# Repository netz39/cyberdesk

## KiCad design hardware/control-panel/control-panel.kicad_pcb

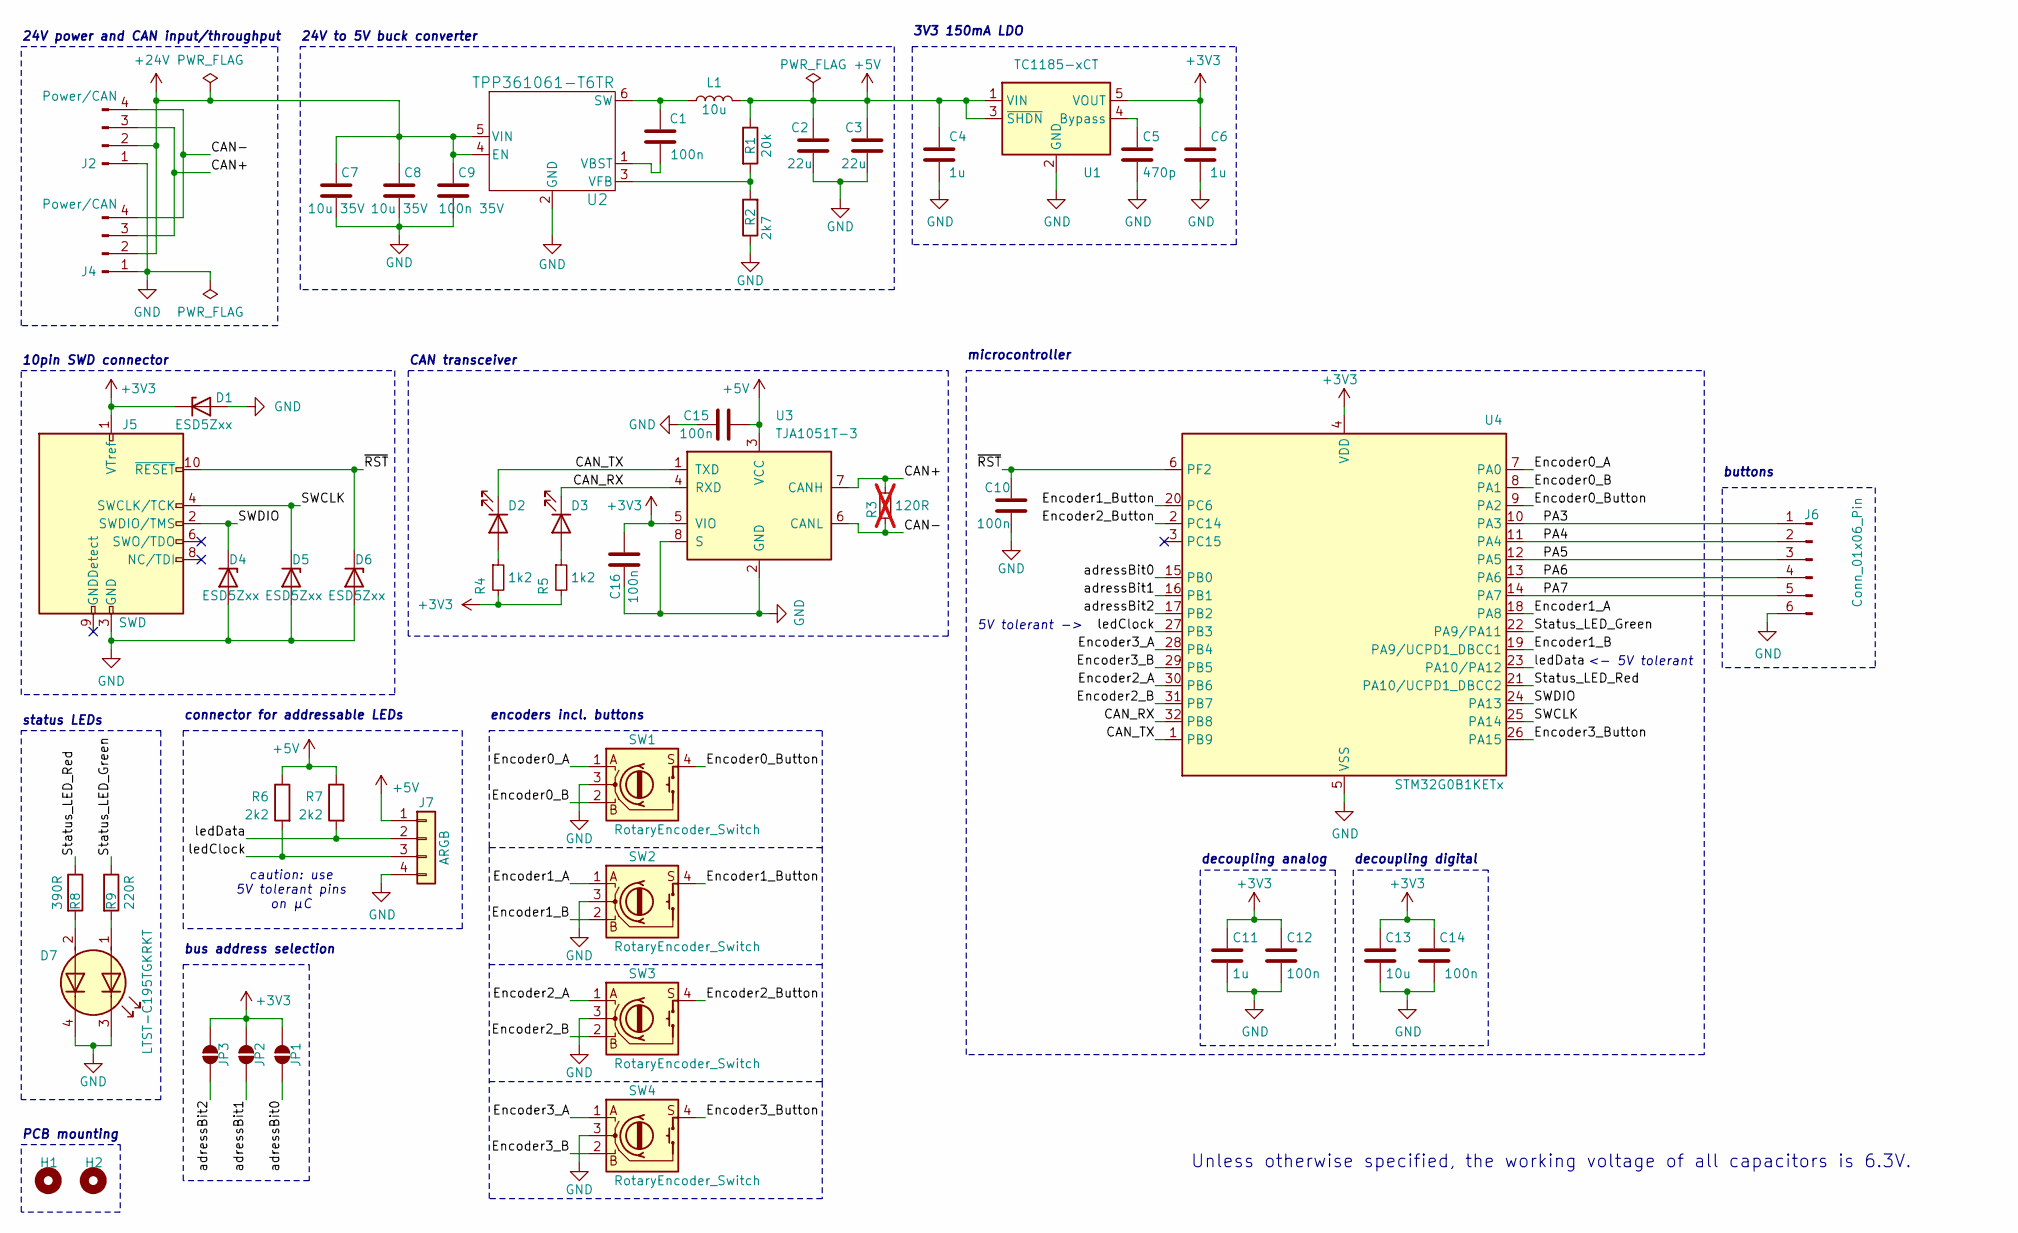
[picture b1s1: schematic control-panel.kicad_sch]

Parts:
C1, C10, C12, C14, C15, C16: 100n; C_0603_1608Metric_Pad1.08x0.95mm_HandSolder
C2, C3: 22u; C_0805_2012Metric_Pad1.18x1.45mm_HandSolder
C4, C6, C11: 1u; C_0805_2012Metric_Pad1.18x1.45mm_HandSolder
C5: 470p; C_0402_1005Metric_Pad0.74x0.62mm_HandSolder
C7, C8: 10u 35V; C_0603_1608Metric_Pad1.08x0.95mm_HandSolder
C9: 100n 35V; C_0603_1608Metric_Pad1.08x0.95mm_HandSolder
C13: 10u; C_0805_2012Metric_Pad1.18x1.45mm_HandSolder
D1, D4, D5, D6: ESD5Zxx; D_SOD-523
D2, D3: 150060BS75000; LED_0603_1608Metric_Pad1.05x0.95mm_HandSolder
D7: LTST-C195TGKRKT; LED_LiteOn_LTST-C195TGKRKT
H1, H2: MountingHole; MountingHole_3.2mm_M3_ISO14580
J2, J4: Power/CAN; Molex_PicoBlade_53047-0410_1x04_P1.25mm_Vertical
J5: SWD; PinHeader_2x05_P1.27mm_Vertical_SMD
J6: Conn_01x06_Pin; Molex_PicoBlade_53047-0610_1x06_P1.25mm_Vertical
J7: ARGB; Molex_PicoBlade_53047-0410_1x04_P1.25mm_Vertical
JP1, JP2, JP3: SolderJumper_2_Open; SolderJumper-2_P1.3mm_Open_TrianglePad1.0x1.5mm
L1: 10u; L_1210_3225Metric_Pad1.42x2.65mm_HandSolder
R1: 20k; R_0603_1608Metric_Pad0.98x0.95mm_HandSolder
R2: 2k7; R_0603_1608Metric_Pad0.98x0.95mm_HandSolder
R3: 120R; R_0603_1608Metric_Pad0.98x0.95mm_HandSolder; not fitted
R4, R5: 1k2; R_0603_1608Metric_Pad0.98x0.95mm_HandSolder
R6, R7: 2k2; R_0603_1608Metric_Pad0.98x0.95mm_HandSolder
R8: 390R; R_0603_1608Metric_Pad0.98x0.95mm_HandSolder
R9: 220R; R_0603_1608Metric_Pad0.98x0.95mm_HandSolder
SW1, SW2, SW3, SW4: RotaryEncoder_Switch; Molex_PicoBlade_53047-0410_1x04_P1.25mm_Vertical
U1: TC1185-xCT; SOT-23-5_HandSoldering
U2: TPP361061-T6TR; SOT-23-6_Handsoldering
U3: TJA1051T-3; SOIC-8_3.9x4.9mm_P1.27mm
U4: STM32G0B1KETx; LQFP-32_7x7mm_P0.8mm

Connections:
+3V3: C6.1, C11.1, C12.1, C13.2, C14.2, C16.1, D1.1 (K), J5.1 (VTref), JP1.1 (A), JP2.1 (A), JP3.1 (A), R4.2, R5.2, U1.5 (VOUT), U3.5 (VIO), U4.4 (VDD)
+5V: C2.2, C3.2, C4.1, C15.1, J7.1, L1.2, R1.1, R6.1, R7.1, U1.1 (VIN), U1.3 (~SHDN), U3.3 (VCC)
+24V: C7.2, C8.2, C9.2, J2.2, J4.2, U2.4 (EN), U2.5 (VIN)
/CAN+: J2.3, J4.3, R3.1, U3.7 (CANH)
/CAN-: J2.4, J4.4, R3.2, U3.6 (CANL)
/CAN_RX: D3.1 (K), U3.4 (RXD), U4.32 (PB8)
/CAN_TX: D2.1 (K), U3.1 (TXD), U4.1 (PB9)
/Encoder0_A: SW1.1 (A), U4.7 (PA0)
/Encoder0_B: SW1.2 (B), U4.8 (PA1)
/Encoder0_Button: SW1.4 (S), U4.9 (PA2)
/Encoder1_A: SW2.1 (A), U4.18 (PA8)
/Encoder1_B: SW2.2 (B), U4.19 (PA9/UCPD1_DBCC1)
/Encoder1_Button: SW2.4 (S), U4.20 (PC6)
/Encoder2_A: SW3.1 (A), U4.30 (PB6)
/Encoder2_B: SW3.2 (B), U4.31 (PB7)
/Encoder2_Button: SW3.4 (S), U4.2 (PC14)
/Encoder3_A: SW4.1 (A), U4.28 (PB4)
/Encoder3_B: SW4.2 (B), U4.29 (PB5)
/Encoder3_Button: SW4.4 (S), U4.26 (PA15)
/PA3: J6.1, U4.10 (PA3)
/PA4: J6.2, U4.11 (PA4)
/PA5: J6.3, U4.12 (PA5)
/PA6: J6.4, U4.13 (PA6)
/PA7: J6.5, U4.14 (PA7)
/SWCLK: D5.1 (K), J5.4 (SWCLK/TCK), U4.25 (PA14)
/SWDIO: D4.1 (K), J5.2 (SWDIO/TMS), U4.24 (PA13)
/Status_LED_Green: R9.1, U4.22 (PA9/PA11)
/Status_LED_Red: R8.1, U4.21 (PA10/UCPD1_DBCC2)
/adressBit0: JP1.2 (B), U4.15 (PB0)
/adressBit1: JP2.2 (B), U4.16 (PB1)
/adressBit2: JP3.2 (B), U4.17 (PB2)
/ledClock: J7.3, R6.2, U4.27 (PB3)
/ledData: J7.2, R7.2, U4.23 (PA10/PA12)
/~RST: C10.1, D6.1 (K), J5.10 (~RESET), U4.6 (PF2)
GND: C2.1, C3.1, C4.2, C5.2, C6.2, C7.1, C8.1, C9.1, C10.2, C11.2, C12.2, C13.1, C14.1, C15.2, C16.2, D1.2 (A), D4.2 (A), D5.2 (A), D6.2 (A), D7.3 (K1), D7.4 (K2), J2.1, J4.1, J5.3 (GND), J5.5 (GND), J6.6, J7.4, R2.1, SW1.3 (C), SW2.3 (C), SW3.3 (C), SW4.3 (C), U1.2 (GND), U2.2 (GND), U3.2 (GND), U3.8 (S), U4.5 (VSS)
unnamed: D2.2 (A), R4.1
unnamed: D3.2 (A), R5.1
unnamed: D7.1 (A1), R9.2
unnamed: D7.2 (A2), R8.2
unnamed: C5.1, U1.4 (Bypass)
unnamed: C1.2, L1.1, U2.6 (SW)
unnamed: C1.1, U2.1 (VBST)
unnamed: R1.2, R2.2, U2.3 (VFB)

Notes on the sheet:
decoupling analog
encoders incl. buttons
3V3 150mA LDO
24V power and CAN input/throughput
microcontroller
CAN transceiver
PCB mounting
5V tolerant ->
connector for addressable LEDs
Unless otherwise specified, the working voltage of all capacitors is 6.3V.
status LEDs
buttons
bus address selection
24V to 5V buck converter
<- 5V tolerant
caution: use 5V tolerant pins on µC
10pin SWD connector
decoupling digital

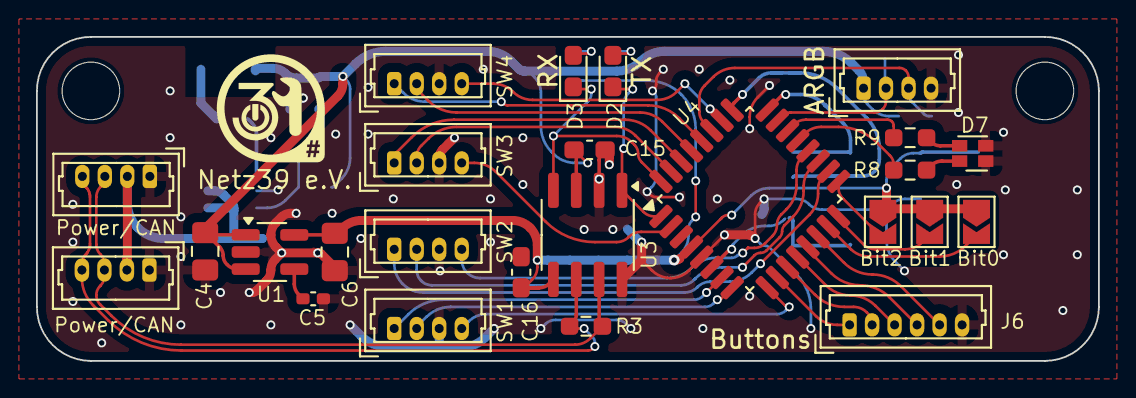
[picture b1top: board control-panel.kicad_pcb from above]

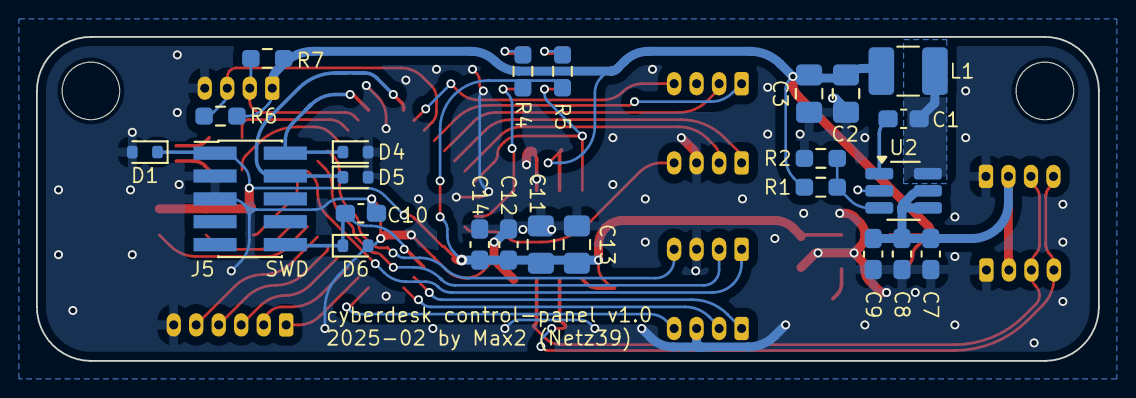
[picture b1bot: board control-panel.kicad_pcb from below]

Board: 2 copper layers, 59.0 x 18.0 mm, 51 parts (24 on the bottom side), 43 nets.

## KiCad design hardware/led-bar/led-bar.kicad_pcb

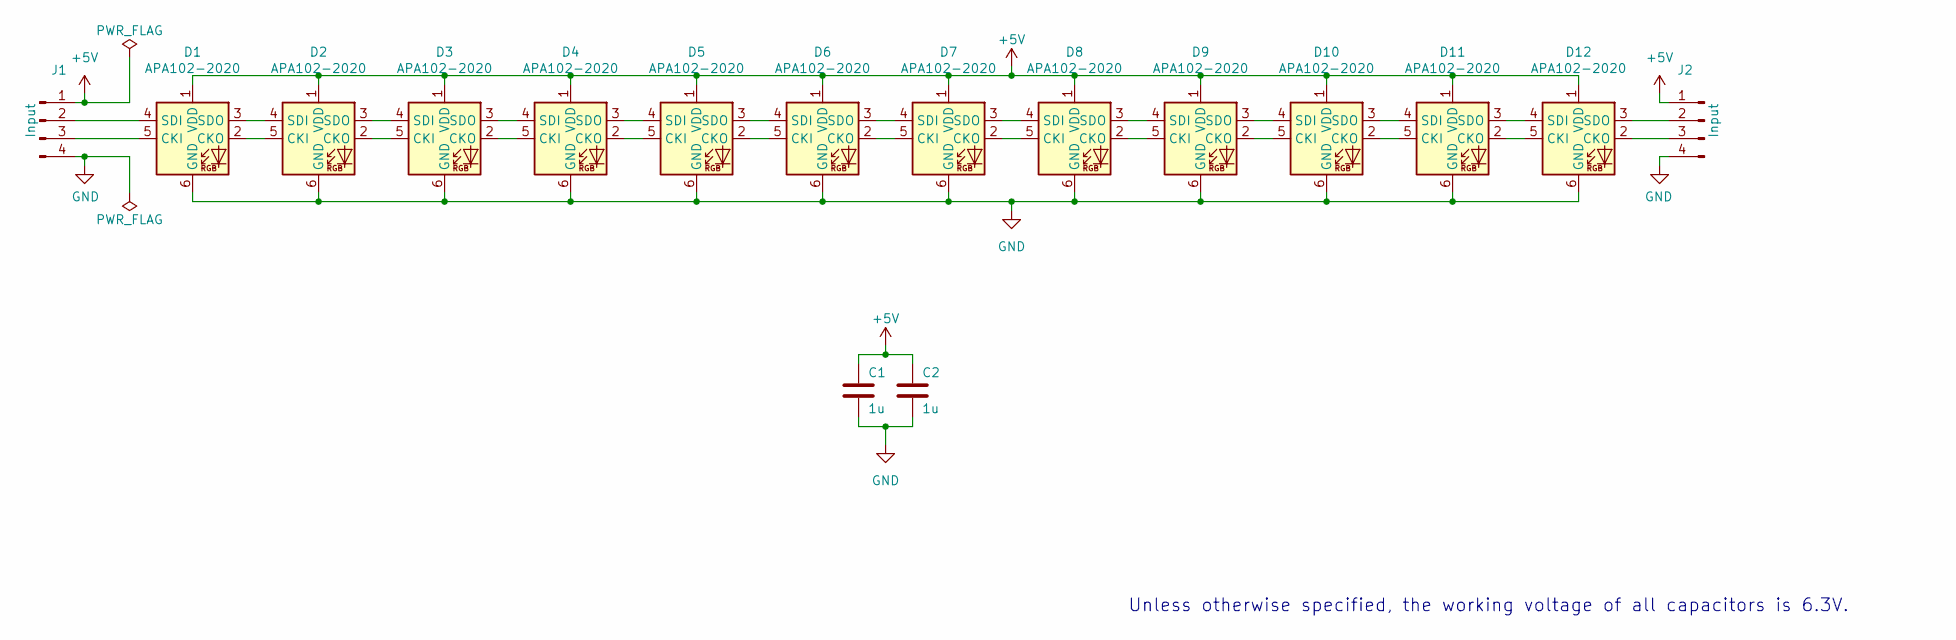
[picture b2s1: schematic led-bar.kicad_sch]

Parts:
C1, C2: 1u; C_0805_2012Metric_Pad1.18x1.45mm_HandSolder
D1, D2, D3, D4, D5, D6, D7, D8, D9, D10, D11, D12: APA102-2020; LED-APA102-2020
J1, J2: Input; SMD_4xSolderPads_2,5mm_1mm

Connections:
+5V: C1.1, C2.1, D1.1 (VDD), D2.1 (VDD), D3.1 (VDD), D4.1 (VDD), D5.1 (VDD), D6.1 (VDD), D7.1 (VDD), D8.1 (VDD), D9.1 (VDD), D10.1 (VDD), D11.1 (VDD), D12.1 (VDD), J1.1, J2.1
GND: C1.2, C2.2, D1.6 (GND), D2.6 (GND), D3.6 (GND), D4.6 (GND), D5.6 (GND), D6.6 (GND), D7.6 (GND), D8.6 (GND), D9.6 (GND), D10.6 (GND), D11.6 (GND), D12.6 (GND), J1.4, J2.4
unnamed: D1.5 (CKI), J1.3
unnamed: D1.2 (CKO), D2.5 (CKI)
unnamed: D1.4 (SDI), J1.2
unnamed: D1.3 (SDO), D2.4 (SDI)
unnamed: D2.2 (CKO), D3.5 (CKI)
unnamed: D2.3 (SDO), D3.4 (SDI)
unnamed: D3.2 (CKO), D4.5 (CKI)
unnamed: D3.3 (SDO), D4.4 (SDI)
unnamed: D4.2 (CKO), D5.5 (CKI)
unnamed: D4.3 (SDO), D5.4 (SDI)
unnamed: D5.2 (CKO), D6.5 (CKI)
unnamed: D5.3 (SDO), D6.4 (SDI)
unnamed: D6.2 (CKO), D7.5 (CKI)
unnamed: D6.3 (SDO), D7.4 (SDI)
unnamed: D7.2 (CKO), D8.5 (CKI)
unnamed: D7.3 (SDO), D8.4 (SDI)
unnamed: D8.2 (CKO), D9.5 (CKI)
unnamed: D8.3 (SDO), D9.4 (SDI)
unnamed: D9.2 (CKO), D10.5 (CKI)
unnamed: D10.2 (CKO), D11.5 (CKI)
unnamed: D9.3 (SDO), D10.4 (SDI)
unnamed: D10.3 (SDO), D11.4 (SDI)
unnamed: D11.2 (CKO), D12.5 (CKI)
unnamed: D11.3 (SDO), D12.4 (SDI)
unnamed: D12.2 (CKO), J2.3
unnamed: D12.3 (SDO), J2.2

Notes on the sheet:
Unless otherwise specified, the working voltage of all capacitors is 6.3V.

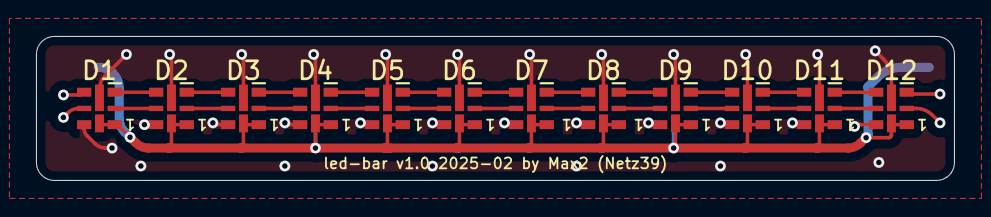
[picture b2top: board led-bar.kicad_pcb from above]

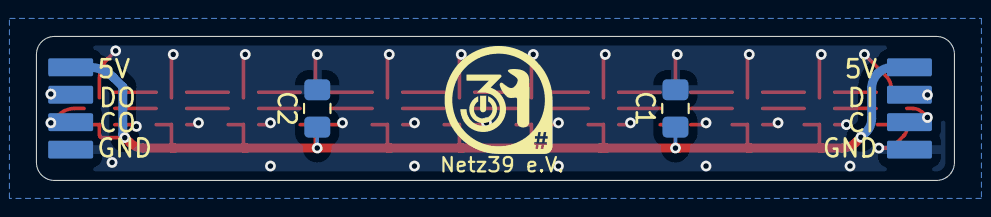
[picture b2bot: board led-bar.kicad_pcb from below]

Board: 2 copper layers, 51.0 x 8.0 mm, 16 parts (4 on the bottom side), 28 nets.

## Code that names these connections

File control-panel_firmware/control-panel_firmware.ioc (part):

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Mcu.Name=STM32G0B1K(B-C-E)Tx
Mcu.Package=LQFP32
Mcu.UserName=STM32G0B1KETx
PA0.GPIOParameters=GPIO_Label
PA0.GPIO_Label=Encoder0_A
PA0.Signal=S_TIM2_CH1_ETR
PA1.GPIOParameters=GPIO_Label
PA1.GPIO_Label=Encoder0_B
PA1.Signal=S_TIM2_CH2
PA10.GPIOParameters=GPIO_Label
PA10.GPIO_Label=ledRed
PA10.Signal=S_TIM1_CH3
PA11\ [PA9].GPIOParameters=GPIO_Label
PA11\ [PA9].GPIO_Label=ledGreen
PA11\ [PA9].Signal=S_TIM1_CH4
PA12\ [PA10].Signal=SPI1_MOSI
PA13.Mode=Serial_Wire
PA13.Signal=SYS_SWDIO
PA14-BOOT0.Mode=Serial_Wire
PA14-BOOT0.Signal=SYS_SWCLK
PA15.GPIOParameters=GPIO_Label
PA15.GPIO_Label=Encoder2_Button
PA15.Signal=GPIO_Input
PA2.GPIOParameters=GPIO_Label
PA2.GPIO_Label=Encoder0_Button
PA2.Signal=GPIO_Input
PA8.GPIOParameters=GPIO_Label
PA8.GPIO_Label=Encoder1_A
PA8.Signal=S_TIM1_CH1
PA9.GPIOParameters=GPIO_Label
PA9.GPIO_Label=Encoder1_B
PA9.Signal=S_TIM1_CH2
PB0.GPIOParameters=GPIO_PuPd,GPIO_Label
PB0.GPIO_Label=addressBit0
PB0.GPIO_PuPd=GPIO_PULLDOWN
PB0.Signal=GPIO_Input
PB1.GPIOParameters=GPIO_PuPd,GPIO_Label
PB1.GPIO_Label=addressBit1
PB1.GPIO_PuPd=GPIO_PULLDOWN
PB1.Signal=GPIO_Input
PB2.GPIOParameters=GPIO_PuPd,GPIO_Label
PB2.GPIO_Label=addressBit2
PB2.GPIO_PuPd=GPIO_PULLDOWN
PB2.Signal=GPIO_Input
PB3.Signal=SPI1_SCK
PB4.GPIOParameters=GPIO_PuPd,GPIO_Label
PB4.GPIO_Label=Encoder2_A
PB4.GPIO_PuPd=GPIO_PULLUP
PB4.Signal=S_TIM3_CH1
PB5.GPIOParameters=GPIO_PuPd,GPIO_Label
PB5.GPIO_Label=Encoder2_B
PB5.GPIO_PuPd=GPIO_PULLUP
PB5.Signal=S_TIM3_CH2
PB6.GPIOParameters=GPIO_PuPd,GPIO_Label
PB6.GPIO_Label=Encoder3_A
PB6.GPIO_PuPd=GPIO_PULLUP
PB6.Signal=S_TIM4_CH1
PB7.GPIOParameters=GPIO_PuPd,GPIO_Label
PB7.GPIO_Label=Encoder3_B
PB7.GPIO_PuPd=GPIO_PULLUP
PB7.Signal=S_TIM4_CH2
PB8.Mode=FDCAN_Activate
PB8.Signal=FDCAN1_RX
PB9.Mode=FDCAN_Activate
PB9.Signal=FDCAN1_TX
PC14-OSC32_IN\ (PC14).GPIOParameters=GPIO_Label
PC14-OSC32_IN\ (PC14).GPIO_Label=Encoder3_Button
PC14-OSC32_IN\ (PC14).Signal=GPIO_Input
PC6.GPIOParameters=GPIO_Label
PC6.GPIO_Label=Encoder1_Button
PC6.Signal=GPIO_Input
RCC.HSE_VALUE=8000000
RCC.SYSCLKFreq_VALUE=16000000
board=custom

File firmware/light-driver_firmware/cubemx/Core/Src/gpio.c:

/* USER CODE BEGIN Header */
/**
  ******************************************************************************
  * @file    gpio.c
  * @brief   This file provides code for the configuration
  *          of all used GPIO pins.
  ******************************************************************************
  * @attention
  *
  * Copyright (c) 2025 STMicroelectronics.
  * All rights reserved.
  *
  * This software is licensed under terms that can be found in the LICENSE file
  * in the root directory of this software component.
  * If no LICENSE file comes with this software, it is provided AS-IS.
  *
  ******************************************************************************
  */
/* USER CODE END Header */

/* Includes ------------------------------------------------------------------*/
#include "gpio.h"

/* USER CODE BEGIN 0 */

/* USER CODE END 0 */

/*----------------------------------------------------------------------------*/
/* Configure GPIO                                                             */
/*----------------------------------------------------------------------------*/
/* USER CODE BEGIN 1 */

/* USER CODE END 1 */

/** Configure pins
     PA12 [PA10]   ------> SPI1_MOSI
     PB3   ------> SPI1_SCK
*/
void MX_GPIO_Init(void)
{

  GPIO_InitTypeDef GPIO_InitStruct = {0};

  /* GPIO Ports Clock Enable */
  __HAL_RCC_GPIOB_CLK_ENABLE();
  __HAL_RCC_GPIOC_CLK_ENABLE();
  __HAL_RCC_GPIOF_CLK_ENABLE();
  __HAL_RCC_GPIOA_CLK_ENABLE();

  /*Configure GPIO pins : PC14 PC15 PC6 */
  GPIO_InitStruct.Pin = GPIO_PIN_14|GPIO_PIN_15|GPIO_PIN_6;
  GPIO_InitStruct.Mode = GPIO_MODE_ANALOG;
  GPIO_InitStruct.Pull = GPIO_NOPULL;
  HAL_GPIO_Init(GPIOC, &GPIO_InitStruct);

  /*Configure GPIO pin : PF2 */
  GPIO_InitStruct.Pin = GPIO_PIN_2;
  GPIO_InitStruct.Mode = GPIO_MODE_ANALOG;
  GPIO_InitStruct.Pull = GPIO_NOPULL;
  HAL_GPIO_Init(GPIOF, &GPIO_InitStruct);

  /*Configure GPIO pins : PA0 PA1 PA2 PA3
                           PA4 PA5 PA6 PA7
                           PA10 PA11 PA15 */
  GPIO_InitStruct.Pin = GPIO_PIN_0|GPIO_PIN_1|GPIO_PIN_2|GPIO_PIN_3
                          |GPIO_PIN_4|GPIO_PIN_5|GPIO_PIN_6|GPIO_PIN_7
                          |GPIO_PIN_10|GPIO_PIN_11|GPIO_PIN_15;
  GPIO_InitStruct.Mode = GPIO_MODE_ANALOG;
  GPIO_InitStruct.Pull = GPIO_NOPULL;
  HAL_GPIO_Init(GPIOA, &GPIO_InitStruct);

  /*Configure GPIO pins : addressBit0_Pin addressBit1_Pin addressBit2_Pin */
  GPIO_InitStruct.Pin = addressBit0_Pin|addressBit1_Pin|addressBit2_Pin;
  GPIO_InitStruct.Mode = GPIO_MODE_INPUT;
  GPIO_InitStruct.Pull = GPIO_PULLDOWN;
  HAL_GPIO_Init(GPIOB, &GPIO_InitStruct);

  /*Configure GPIO pin : PA12 */
  GPIO_InitStruct.Pin = GPIO_PIN_12;
  GPIO_InitStruct.Mode = GPIO_MODE_AF_PP;
  GPIO_InitStruct.Pull = GPIO_NOPULL;
  GPIO_InitStruct.Speed = GPIO_SPEED_FREQ_LOW;
  GPIO_InitStruct.Alternate = GPIO_AF0_SPI1;
  HAL_GPIO_Init(GPIOA, &GPIO_InitStruct);

  /*Configure GPIO pin : PB3 */
  GPIO_InitStruct.Pin = GPIO_PIN_3;
  GPIO_InitStruct.Mode = GPIO_MODE_AF_PP;
  GPIO_InitStruct.Pull = GPIO_NOPULL;
  GPIO_InitStruct.Speed = GPIO_SPEED_FREQ_LOW;
  GPIO_InitStruct.Alternate = GPIO_AF0_SPI1;
  HAL_GPIO_Init(GPIOB, &GPIO_InitStruct);

}

/* USER CODE BEGIN 2 */

/* USER CODE END 2 */

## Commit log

2025-02-07 Init project
2025-02-09 Finish light-driver hardware
2025-02-09 Finish control panel
2025-02-09 Create two subfolders to keep hardware and firmware separate
2025-02-10 Update footprints to given in inventory
2025-02-10 Add addressable LED bar
2025-02-10 Add notes
2025-02-23 Update some values
2025-02-25 Init firmware projects with Hello-World LED blinking
2025-02-25 Add CAN interface and basic message handling
2025-02-25 Add message processor
2025-02-25 Add basic LED strip control
2025-02-26 Add fading for LED strip
2025-02-26 Control LED strip over CAN
2025-02-26 Some refactorings
2025-02-26 Use array for LED strips
2025-02-27 Add feedback bar with addressable LEDs
2025-02-27 Add fault handlers to malloc failed and stack overflow hooks
2025-02-27 Add encoder, state machine and CAN sender
2025-02-27 Fix various bugs
2025-09-30 Improve UI handling by reducing from two encoder to single one, switch between brightness and color mode with encoder button. Turn on/off strip with dedicated power button.
2025-10-01 Deattach timers from unused encoders to use PWM for status LED
2025-10-03 Improve turn on behaviour
2025-10-04 Improve fading so each LED has individual fading window
2025-11-06 Add 3D model
2026-04-12 Improve CAN ID handling/decoding
2026-04-13 Add support for sending global messages
2026-04-13 Change default color
2026-04-13 Fix CAN ID decoding
2026-04-13 Fix CAN FIFO overload
2026-04-13 Enable stack highmarking and increase default task stack size
2026-04-13 Reset brightness/color temperature after being off some time
2026-04-13 Add .history (introduced by KiCad 10) to gitignore
2026-04-13 Update util submodule
2026-04-13 Add timeout in color change mode
